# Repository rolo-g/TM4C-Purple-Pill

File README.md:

# TM4C-Red-Pill

The schematic and PCB can be viewed without installing KiCad 8.0 by using [KiCanvas, an online KiCad viewer](https://github.com/theacodes/kicanvas)

https://kicanvas.org/?github=https%3A%2F%2Fgithub.com%2Frolo-g%2FTM4C-Red-Pill

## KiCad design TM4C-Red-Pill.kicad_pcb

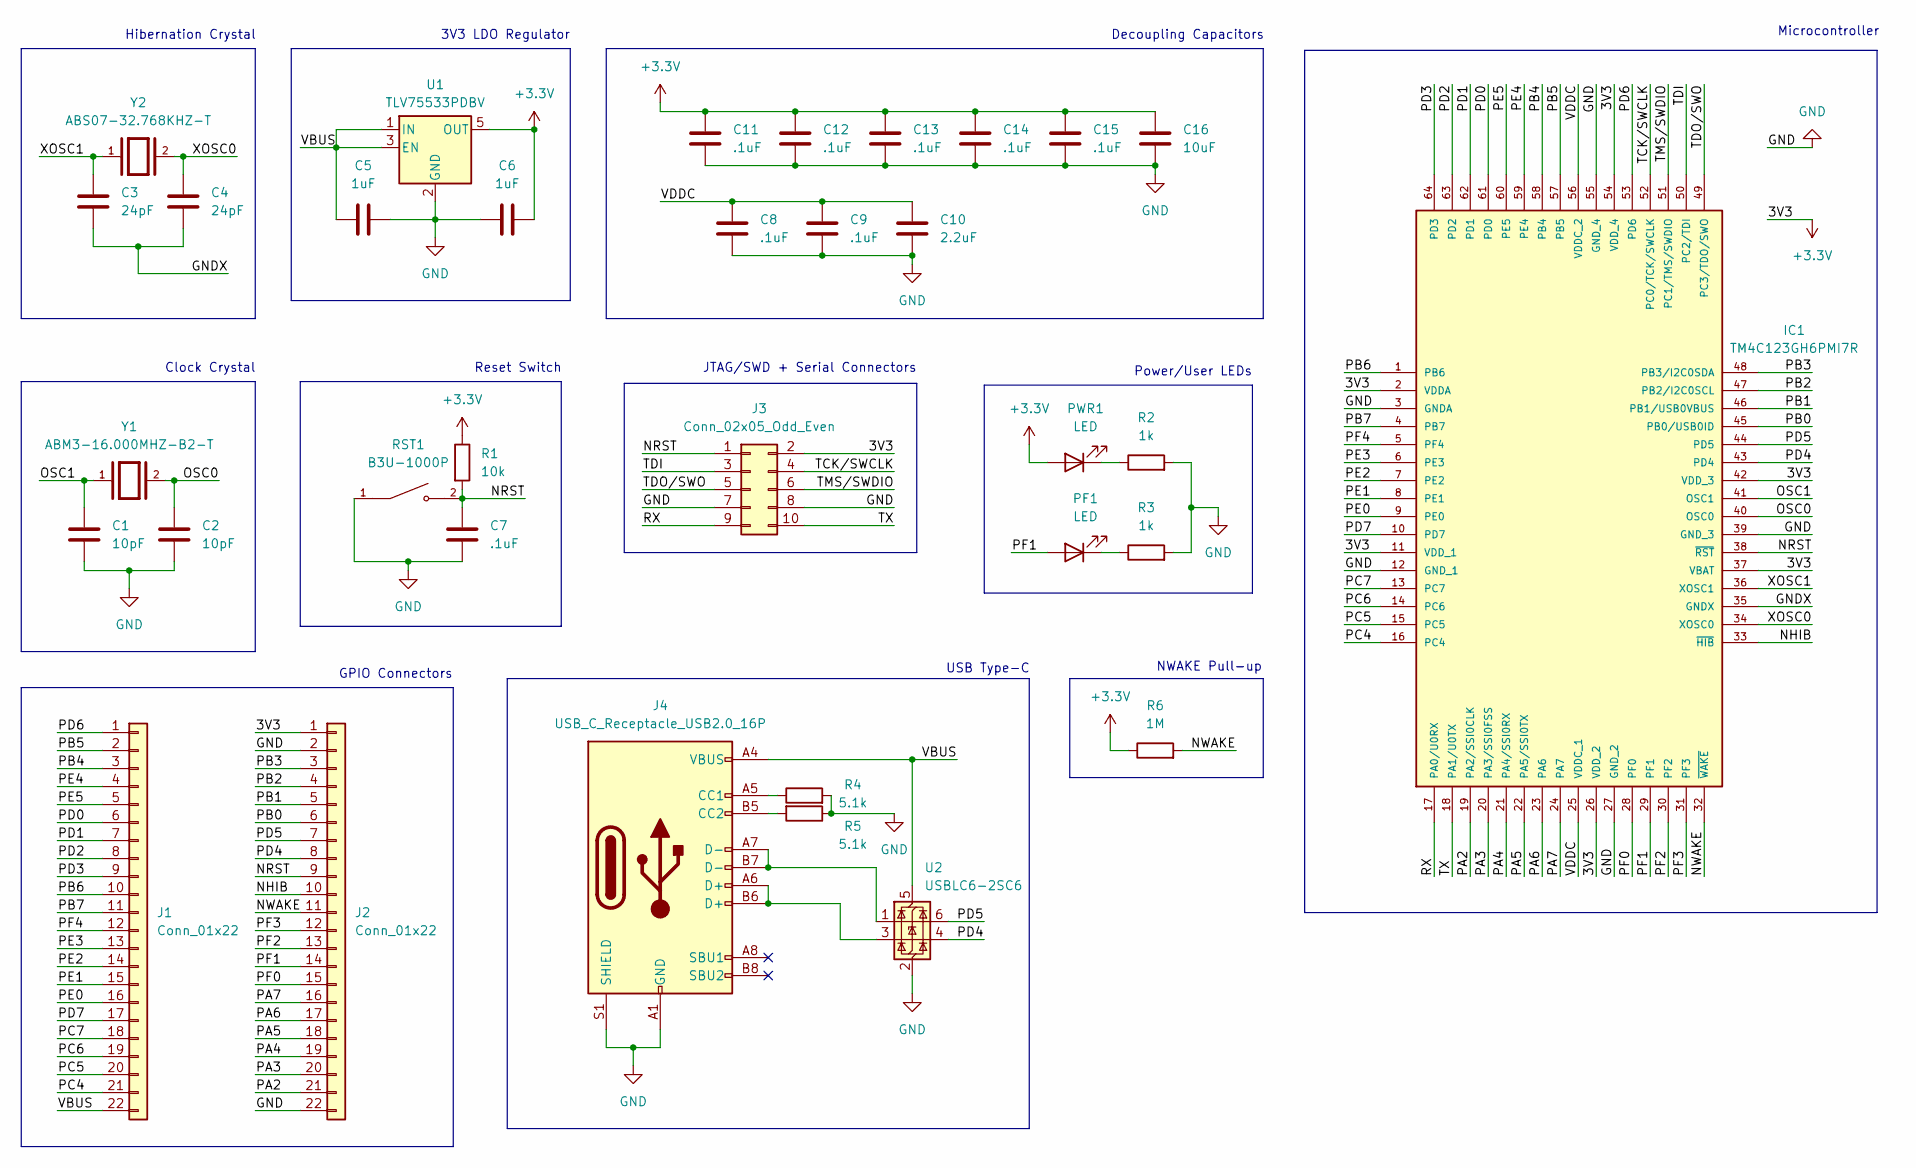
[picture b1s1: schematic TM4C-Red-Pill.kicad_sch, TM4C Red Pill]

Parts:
C1, C2: 10pF; C_0402_1005Metric
C3, C4: 24pF; C_0402_1005Metric
C5, C6: 1uF; C_0603_1608Metric
C7, C8, C9, C11, C12, C13, C14, C15: .1uF; C_0402_1005Metric
C10: 2.2uF; C_0603_1608Metric
C16: 10uF; C_0603_1608Metric
IC1: TM4C123GH6PMI7R; QFP50P1200X1200X160-64N; MOUSER_PART_NUMBER 595-TM4C123GH6PMI7R
J1, J2: Conn_01x22; PinHeader_1x22_P2.54mm_Vertical
J3: Conn_02x05_Odd_Even; PinHeader_2x05_P2.54mm_Horizontal
J4: USB_C_Receptacle_USB2.0_16P; USB_C_Receptacle_G-Switch_GT-USB-7010ASV
PF1: LED; LED_1206_3216Metric
PWR1: LED; LED_1206_3216Metric
R1: 10k; R_0402_1005Metric
R2, R3: 1k; R_0402_1005Metric
R4, R5: 5.1k; R_0402_1005Metric
R6: 1M; R_0402_1005Metric
RST1: B3U-1000P; SW_B3U-1000P
U1: TLV75533PDBV; SOT-23-5
U2: USBLC6-2SC6; SOT-23-6
Y1: ABM3-16.000MHZ-B2-T; XTAL_ABM3-16.000MHZ-B2-T; PARTREV 4/25/2022
Y2: ABS07-32.768KHZ-T; XTAL_ABS07-32.768KHZ-T; PARTREV 08.19.15

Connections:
+3.3V: C6.1, C11.1, C12.1, C13.1, C14.1, C15.1, C16.1, IC1.2 (VDDA), IC1.11 (VDD_1), IC1.26 (VDD_2), IC1.37 (VBAT), IC1.42 (VDD_3), IC1.54 (VDD_4), J2.1, J3.2, PWR1.2 (A), R1.1, R6.1, U1.5 (OUT); also elsewhere on the board
/GNDX: C3.2, C4.2, IC1.35 (GNDX)
/NHIB: IC1.33 (~HIB), J2.10
/NRST: C7.1, IC1.38 (~RST), J2.9, J3.1, R1.2, RST1.2; also elsewhere on the board
/NWAKE: IC1.32 (~WAKE), J2.11, R6.2
/OSC0: C2.1, IC1.40 (OSC0), Y1.2
/OSC1: C1.1, IC1.41 (OSC1), Y1.1
/PA2: IC1.19 (PA2/SSI0CLK), J2.21
/PA3: IC1.20 (PA3/SSI0FSS), J2.20
/PA4: IC1.21 (PA4/SSI0RX), J2.19
/PA5: IC1.22 (PA5/SSI0TX), J2.18
/PA6: IC1.23 (PA6), J2.17
/PA7: IC1.24 (PA7), J2.16
/PB0: IC1.45 (PB0/USB0ID), J2.6
/PB1: IC1.46 (PB1/USB0VBUS), J2.5
/PB2: IC1.47 (PB2/I2C0SCL), J2.4
/PB3: IC1.48 (PB3/I2C0SDA), J2.3
/PB4: IC1.58 (PB4), J1.3
/PB5: IC1.57 (PB5), J1.2
/PB6: IC1.1 (PB6), J1.10
/PB7: IC1.4 (PB7), J1.11
/PC4: IC1.16 (PC4), J1.21
/PC5: IC1.15 (PC5), J1.20
/PC6: IC1.14 (PC6), J1.19
/PC7: IC1.13 (PC7), J1.18
/PD0: IC1.61 (PD0), J1.6
/PD1: IC1.62 (PD1), J1.7
/PD2: IC1.63 (PD2), J1.8
/PD3: IC1.64 (PD3), J1.9
/PD4: IC1.43 (PD4), J2.8, U2.4 (I/O2)
/PD5: IC1.44 (PD5), J2.7, U2.6 (I/O1)
/PD6: IC1.53 (PD6), J1.1
/PD7: IC1.10 (PD7), J1.17
/PE0: IC1.9 (PE0), J1.16
/PE1: IC1.8 (PE1), J1.15
/PE2: IC1.7 (PE2), J1.14
/PE3: IC1.6 (PE3), J1.13
/PE4: IC1.59 (PE4), J1.4
/PE5: IC1.60 (PE5), J1.5
/PF0: IC1.28 (PF0), J2.15
/PF1: IC1.29 (PF1), J2.14, PF1.2 (A)
/PF2: IC1.30 (PF2), J2.13
/PF3: IC1.31 (PF3), J2.12
/PF4: IC1.5 (PF4), J1.12
/RX: IC1.17 (PA0/U0RX), J3.9
/TCK/SWCLK: IC1.52 (PC0/TCK/SWCLK), J3.4
/TDI: IC1.50 (PC2/TDI), J3.3
/TDO/SWO: IC1.49 (PC3/TDO/SWO), J3.5
/TMS/SWDIO: IC1.51 (PC1/TMS/SWDIO), J3.6
/TX: IC1.18 (PA1/U0TX), J3.10
/VBUS: C5.2, J1.22, J4.A4 (VBUS), J4.A9 (VBUS), J4.B4 (VBUS), J4.B9 (VBUS), U1.1 (IN), U1.3 (EN), U2.5 (VBUS)
/VDDC: C8.1, C9.1, C10.1, IC1.25 (VDDC_1), IC1.56 (VDDC_2)
/XOSC0: C4.1, IC1.34 (XOSC0), Y2.2
/XOSC1: C3.1, IC1.36 (XOSC1), Y2.1
GND: C1.2, C2.2, C5.1, C6.2, C7.2, C8.2, C9.2, C10.2, C11.2, C12.2, C13.2, C14.2, C15.2, C16.2, IC1.3 (GNDA), IC1.12 (GND_1), IC1.27 (GND_2), IC1.39 (GND_3), IC1.55 (GND_4), J2.2, J2.22, J3.7, J3.8, J4.A1 (GND), J4.A12 (GND), J4.B1 (GND), J4.B12 (GND), J4.S1 (SHIELD), R2.2, R3.2, R4.2, R5.1, RST1.1, U1.2 (GND), U2.2 (GND); also elsewhere on the board
unnamed: J4.A5 (CC1), R4.1
unnamed: J4.B5 (CC2), R5.2
unnamed: J4.A6 (D+), J4.B6 (D+), U2.3 (I/O2)
unnamed: J4.A7 (D-), J4.B7 (D-), U2.1 (I/O1)
unnamed: PF1.1 (K), R3.1
unnamed 60: PWR1.1 (K), R2.1; also elsewhere on the board

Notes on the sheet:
NWAKE Pull-up
3V3 LDO Regulator
Decoupling Capacitors
Clock Crystal
Power/User LEDs
Hibernation Crystal
USB Type-C
Microcontroller
Reset Switch
JTAG/SWD + Serial Connectors
GPIO Connectors

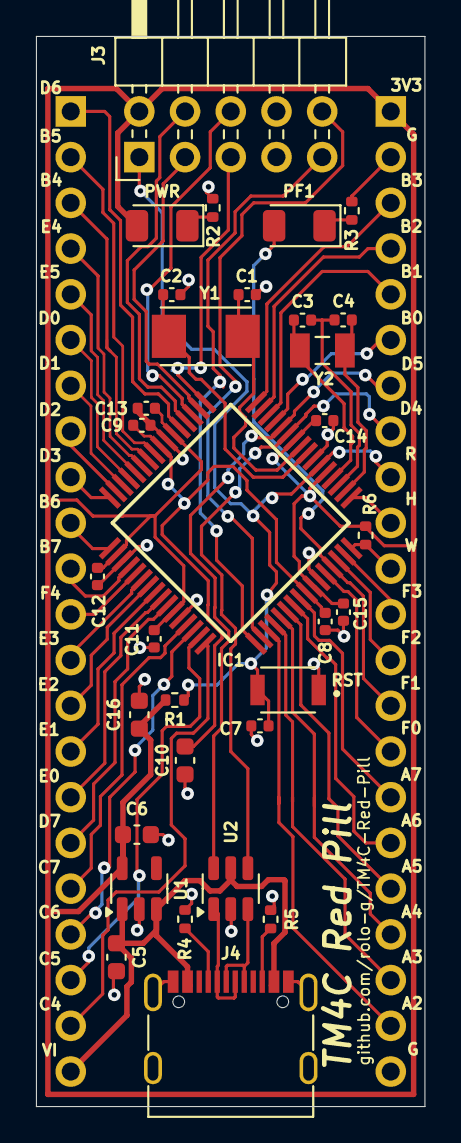
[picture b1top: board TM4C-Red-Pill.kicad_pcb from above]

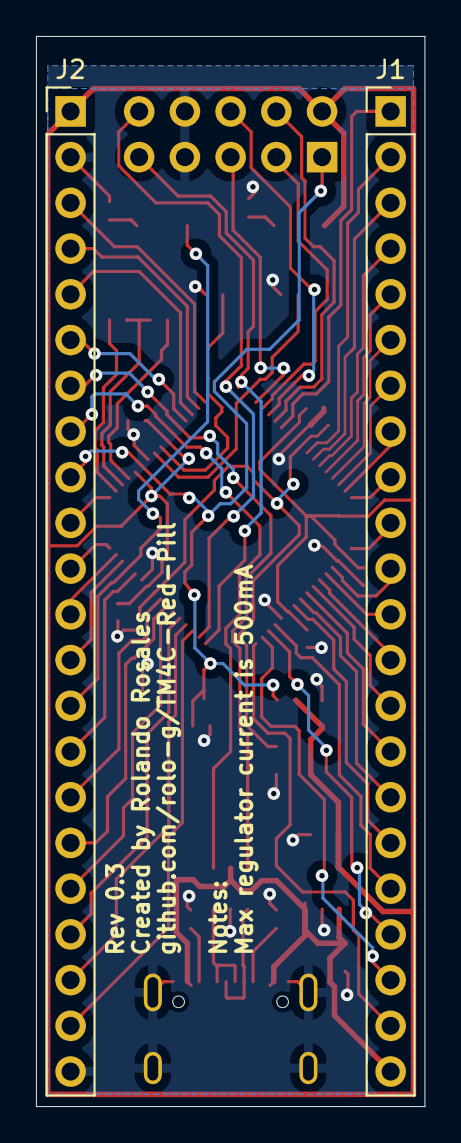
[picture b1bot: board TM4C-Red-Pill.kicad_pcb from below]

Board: 2 copper layers, 21.6 x 59.4 mm, 34 parts (2 on the bottom side), 61 nets.

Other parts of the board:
PWR: LED; LED_1206_3216Metric
RST: B3U-1000P; SW_B3U-1000P

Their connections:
+3.3V: PWR.2 (A); also elsewhere on the board
/NRST: RST.2; also elsewhere on the board
GND: RST.1; also elsewhere on the board
unnamed 60: PWR.1 (K); also elsewhere on the board

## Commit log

2024-05-31 Switch Type-C to Micro-B
2024-06-02 Mostly finishied pinout. Will redo entire PCB with original GPIO configuration, as it is too messy
2024-06-03 Rehauled GPIO pinout. Need to find NRST wiring
2024-06-04 Add image
2024-06-04 Update image
2024-06-16 Revision 0.3 with ground plane
2024-06-16 Create LICENSE
2024-06-16 Update thumbnail image
2024-07-05 Renamed project to TM4C Red Pill
